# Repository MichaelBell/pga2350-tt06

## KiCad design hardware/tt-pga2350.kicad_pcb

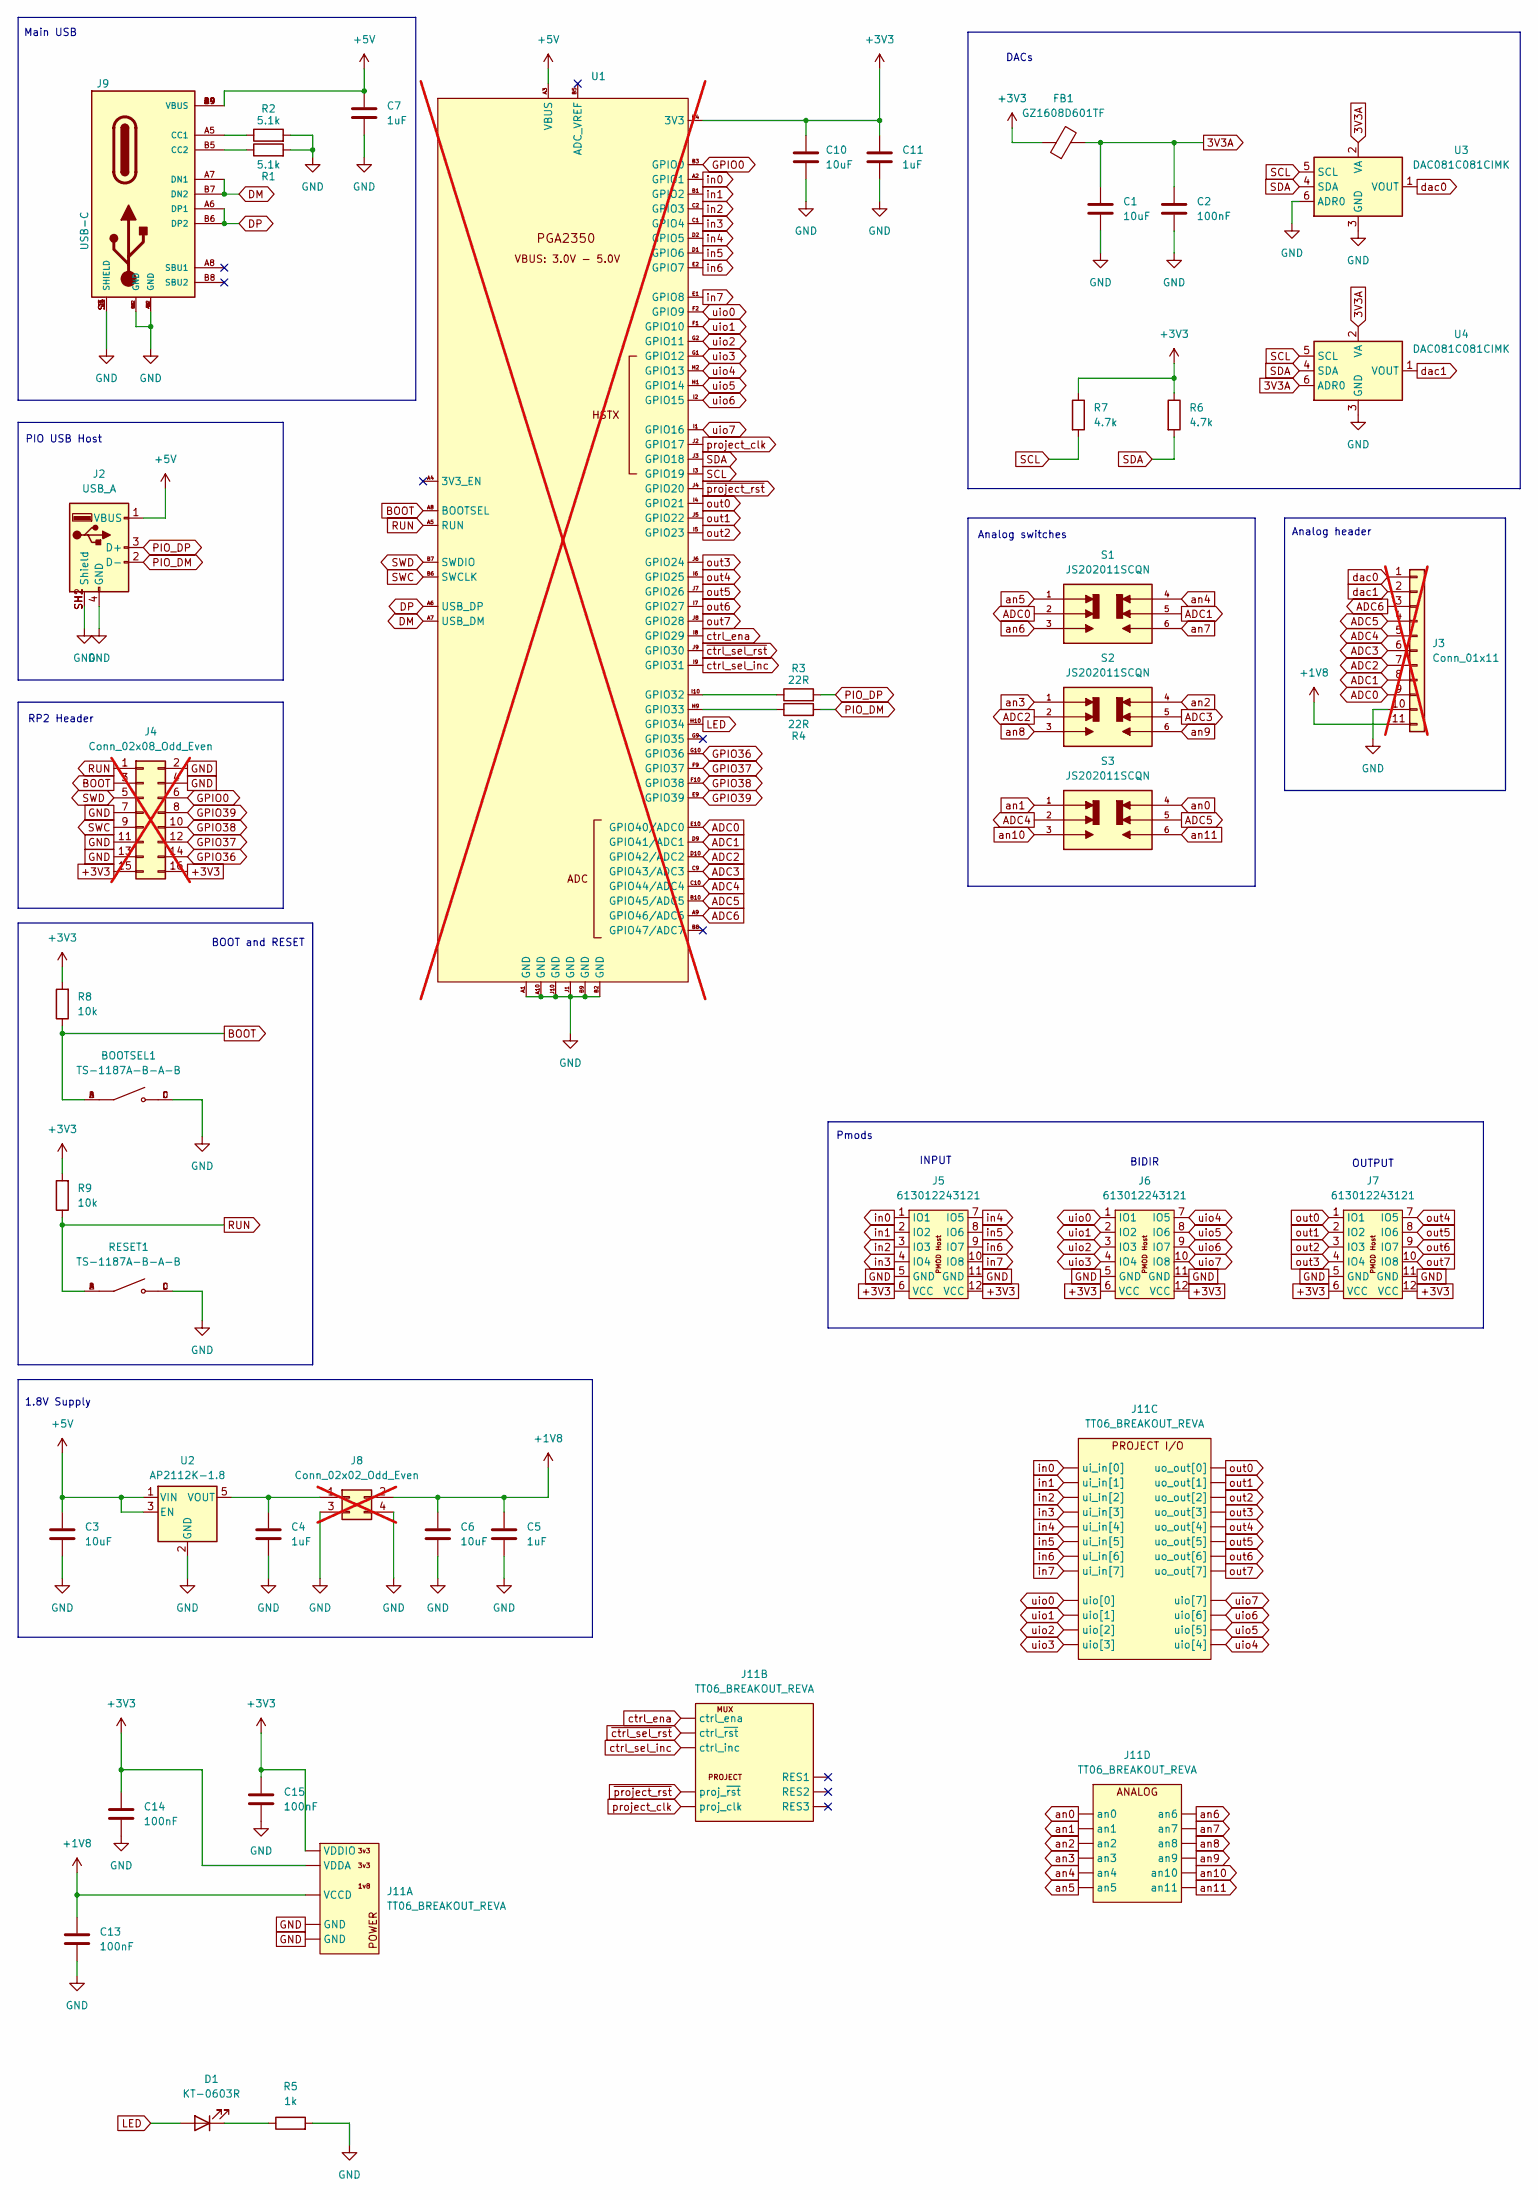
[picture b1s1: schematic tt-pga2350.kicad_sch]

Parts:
BOOTSEL1: TS-1187A-B-A-B; SW_TS-1187A-B-A-B; PARTREV A0
C1, C3, C6, C10: 10uF; C_0603_1608Metric
C2, C13, C14, C15: 100nF; C_0603_1608Metric
C4, C5, C7, C11: 1uF; C_0603_1608Metric
D1: KT-0603R; LED_0603_1608Metric; JLC C2286
FB1: GZ1608D601TF; L_0603_1608Metric
J2: USB_A; TE_292303-1; JLC C86461
J3: Conn_01x11; PinHeader_1x11_P2.54mm_Vertical; not fitted
J4: Conn_02x08_Odd_Even; PinHeader_2x08_P2.54mm_Vertical; not fitted
J5, J6, J7: 613012243121; PinSocket_2x06_P2.54mm_PMODHost1A; LCSC Part # C21262345
J8: Conn_02x02_Odd_Even; PinHeader_2x02_P2.54mm_Vertical; not fitted
J9: USB-C; TYPE-C-SMD_MC-107DJ; MPN USB4500-03-0-A; JLC C3039323
J11: TT06_BREAKOUT_REVA; TT06_CARRIER_ON_DB
R1, R2: 5.1k; R_0603_1608Metric
R3, R4: 22R; R_0603_1608Metric
R5: 1k; R_0603_1608Metric
R6, R7: 4.7k; R_0603_1608Metric
R8, R9: 10k; R_0603_1608Metric
RESET1: TS-1187A-B-A-B; SW_TS-1187A-B-A-B; PARTREV A0
S1, S2, S3: JS202011SCQN; SW_JS202011SCQN; PARTREV 26 May 22
U1: PGA2350; not fitted
U2: AP2112K-1.8; SOT-23-5; JLC C176944
U3, U4: DAC081C081CIMK; SOT-23-6; LCSC Part # C2679618

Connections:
3V3A: C1.1, C2.1, FB1.2, U3.2 (VA), U4.2 (VA), U4.6 (ADR0)
+1V8: C5.1, C6.1, C13.1, J3.11, J8.2, J11.A7 (VCCD)
+3V3: C10.1, C11.1, C14.1, C15.1, FB1.1, J4.15, J4.16, J5.6 (VCC), J5.12 (VCC), J6.6 (VCC), J6.12 (VCC), J7.6 (VCC), J7.12 (VCC), J11.B2 (VDDA), J11.B4 (VDDIO), R6.1, R7.1, R8.2, R9.2, U1.B4 (3V3); also elsewhere on the board
+5V: C3.1, C7.1, J2.1 (VBUS), J9.A4 (VBUS), J9.A9 (VBUS), J9.B4 (VBUS), J9.B9 (VBUS), U1.A3 (VBUS), U2.1 (VIN), U2.3 (EN); also elsewhere on the board
ADC0: J3.9, S1.2, U1.E10 (GPIO40/ADC0); also elsewhere on the board
ADC1: J3.8, S1.5, U1.D9 (GPIO41/ADC1); also elsewhere on the board
ADC2: J3.7, S2.2, U1.D10 (GPIO42/ADC2); also elsewhere on the board
ADC3: J3.6, S2.5, U1.C9 (GPIO43/ADC3); also elsewhere on the board
ADC4: J3.5, S3.2, U1.C10 (GPIO44/ADC4); also elsewhere on the board
ADC5: J3.4, S3.5, U1.B10 (GPIO45/ADC5); also elsewhere on the board
ADC6: J3.3, U1.A9 (GPIO46/ADC6); also elsewhere on the board
BOOT: BOOTSEL1.A, BOOTSEL1.B, J4.3, R8.1, U1.A8 (BOOTSEL); also elsewhere on the board
DM: J9.A7 (DN1), J9.B7 (DN2), U1.A7 (USB_DM); also elsewhere on the board
DP: J9.A6 (DP1), J9.B6 (DP2), U1.A6 (USB_DP); also elsewhere on the board
GND: BOOTSEL1.C, BOOTSEL1.D, C1.2, C2.2, C3.2, C4.2, C5.2, C6.2, C7.2, C10.2, C11.2, C13.2, C14.2, C15.2, J2.4 (GND), J2.SH1 (Shield), J2.SH2 (Shield), J3.10, J4.2, J4.4, J4.7, J4.11, J4.13, J5.5 (GND), J5.11 (GND), J6.5 (GND), J6.11 (GND), J7.5 (GND), J7.11 (GND), J8.3, J8.4, J9.1 (SHIELD), J9.A1 (GND), J9.A12 (GND), J9.B1 (GND), J9.B12 (GND), J9.S1 (SHIELD), J9.S3 (SHIELD), J9.S4 (SHIELD), J11.A1 (GND), J11.A5 (GND), J11.A12 (GND), J11.A15 (GND), J11.A18 (GND), J11.A21 (GND), J11.A23 (GND), J11.A25 (GND), J11.A27 (GND), J11.A29 (GND), J11.A31 (GND), J11.A32 (GND), J11.A33 (GND), J11.A37 (GND), J11.A38 (GND), J11.B1 (GND), J11.B3 (GND), J11.B6 (GND), J11.B8 (GND), J11.B10 (GND), J11.B12 (GND), J11.B14 (GND), J11.B16 (GND), J11.B17 (GND), J11.B18 (GND), J11.B23 (GND), J11.B24 (GND), J11.B29 (GND), J11.B30 (GND), J11.B35 (GND), J11.B36 (GND), J11.B39 (GND), J11.B40 (GND), R1.2, R2.2, R5.2, RESET1.C, RESET1.D, U1.A1 (GND), U1.A10 (GND), U1.B2 (GND), U1.B9 (GND), U1.J1 (GND), U1.J10 (GND), U2.2 (GND), U3.3 (GND), U3.6 (ADR0), U4.3 (GND); also elsewhere on the board
GPIO0: J4.6, U1.B3 (GPIO0); also elsewhere on the board
GPIO36: J4.14, U1.G10 (GPIO36); also elsewhere on the board
GPIO37: J4.12, U1.F9 (GPIO37); also elsewhere on the board
GPIO38: J4.10, U1.F10 (GPIO38); also elsewhere on the board
GPIO39: J4.8, U1.E9 (GPIO39); also elsewhere on the board
LED: D1.2 (A), U1.H10 (GPIO34); also elsewhere on the board
unnamed: D1.1 (K), R5.1
unnamed: C4.1, J8.1, U2.5 (VOUT)
unnamed: J9.A5 (CC1), R2.1
unnamed: J9.B5 (CC2), R1.1
unnamed 25: R3.1, U1.I10 (GPIO32); also elsewhere on the board
unnamed 26: R4.1, U1.H9 (GPIO33); also elsewhere on the board
PIO_DM: J2.2 (D-), R4.2
PIO_DP: J2.3 (D+), R3.2
RUN: J4.1, R9.1, RESET1.A, RESET1.B, U1.A5 (RUN); also elsewhere on the board
SCL: R7.2, U1.I3 (GPIO19), U3.5 (SCL), U4.5 (SCL); also elsewhere on the board
SDA: R6.2, U1.J3 (GPIO18), U3.4 (SDA), U4.4 (SDA); also elsewhere on the board
SWC: J4.9, U1.B6 (SWCLK); also elsewhere on the board
SWD: J4.5, U1.B7 (SWDIO); also elsewhere on the board
an0: J11.A20 (an0), S3.4
an1: J11.A22 (an1), S3.1
an2: J11.A24 (an2), S2.4
an3: J11.A26 (an3), S2.1
an4: J11.A28 (an4), S1.4
an5: J11.A30 (an5), S1.1
an6: J11.B15 (an6), S1.3
an7: J11.B13 (an7), S1.6
an8: J11.B11 (an8), S2.3
an9: J11.B9 (an9), S2.6
an10: J11.B7 (an10), S3.3
an11: J11.B5 (an11), S3.6
ctrl_ena: J11.A2 (ctrl_ena), U1.I8 (GPIO29); also elsewhere on the board
ctrl_sel_inc: J11.A3 (ctrl_inc), U1.I9 (GPIO31); also elsewhere on the board
dac0: J3.1, U3.1 (VOUT)
dac1: J3.2, U4.1 (VOUT)
in0: J5.1 (IO1), J11.A9 (ui_in[0]), U1.A2 (GPIO1); also elsewhere on the board
in1: J5.2 (IO2), J11.A11 (ui_in[1]), U1.B1 (GPIO2); also elsewhere on the board
in2: J5.3 (IO3), J11.A14 (ui_in[2]), U1.C2 (GPIO3); also elsewhere on the board
in3: J5.4 (IO4), J11.A13 (ui_in[3]), U1.C1 (GPIO4); also elsewhere on the board
in4: J5.7 (IO5), J11.A17 (ui_in[4]), U1.D2 (GPIO5); also elsewhere on the board
in5: J5.8 (IO6), J11.A19 (ui_in[5]), U1.D1 (GPIO6); also elsewhere on the board
in6: J5.9 (IO7), J11.A16 (ui_in[6]), U1.E2 (GPIO7); also elsewhere on the board
in7: J5.10 (IO8), J11.A34 (ui_in[7]), U1.E1 (GPIO8); also elsewhere on the board
out0: J7.1 (IO1), J11.B27 (uo_out[0]), U1.I4 (GPIO21); also elsewhere on the board
out1: J7.2 (IO2), J11.B28 (uo_out[1]), U1.J5 (GPIO22); also elsewhere on the board
out2: J7.3 (IO3), J11.B25 (uo_out[2]), U1.I5 (GPIO23); also elsewhere on the board
out3: J7.4 (IO4), J11.B26 (uo_out[3]), U1.J6 (GPIO24); also elsewhere on the board
out4: J7.7 (IO5), J11.B21 (uo_out[4]), U1.I6 (GPIO25); also elsewhere on the board
out5: J7.8 (IO6), J11.B22 (uo_out[5]), U1.J7 (GPIO26); also elsewhere on the board
out6: J7.9 (IO7), J11.B19 (uo_out[6]), U1.I7 (GPIO27); also elsewhere on the board
out7: J7.10 (IO8), J11.B20 (uo_out[7]), U1.J8 (GPIO28); also elsewhere on the board
project_clk: J11.A35 (proj_clk), U1.J2 (GPIO17); also elsewhere on the board
uio0: J6.1 (IO1), J11.A39 (uio[0]), U1.F2 (GPIO9); also elsewhere on the board
uio1: J6.2 (IO2), J11.A40 (uio[1]), U1.F1 (GPIO10); also elsewhere on the board
uio2: J6.3 (IO3), J11.B37 (uio[2]), U1.G2 (GPIO11); also elsewhere on the board
uio3: J6.4 (IO4), J11.B38 (uio[3]), U1.G1 (GPIO12); also elsewhere on the board
uio4: J6.7 (IO5), J11.B33 (uio[4]), U1.H2 (GPIO13); also elsewhere on the board
uio5: J6.8 (IO6), J11.B34 (uio[5]), U1.H1 (GPIO14); also elsewhere on the board
uio6: J6.9 (IO7), J11.B31 (uio[6]), U1.I2 (GPIO15); also elsewhere on the board
uio7: J6.10 (IO8), J11.B32 (uio[7]), U1.I1 (GPIO16); also elsewhere on the board
~ctrl_sel_rst: J11.A4 (ctrl_~rst), U1.J9 (GPIO30); also elsewhere on the board
~project_rst: J11.A36 (proj_~rst), U1.J4 (GPIO20); also elsewhere on the board

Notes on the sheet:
Main USB
BOOT and RESET
1.8V Supply
OUTPUT
Pmods
PIO USB Host
RP2 Header
DACs
Analog switches
BIDIR
Analog header
INPUT

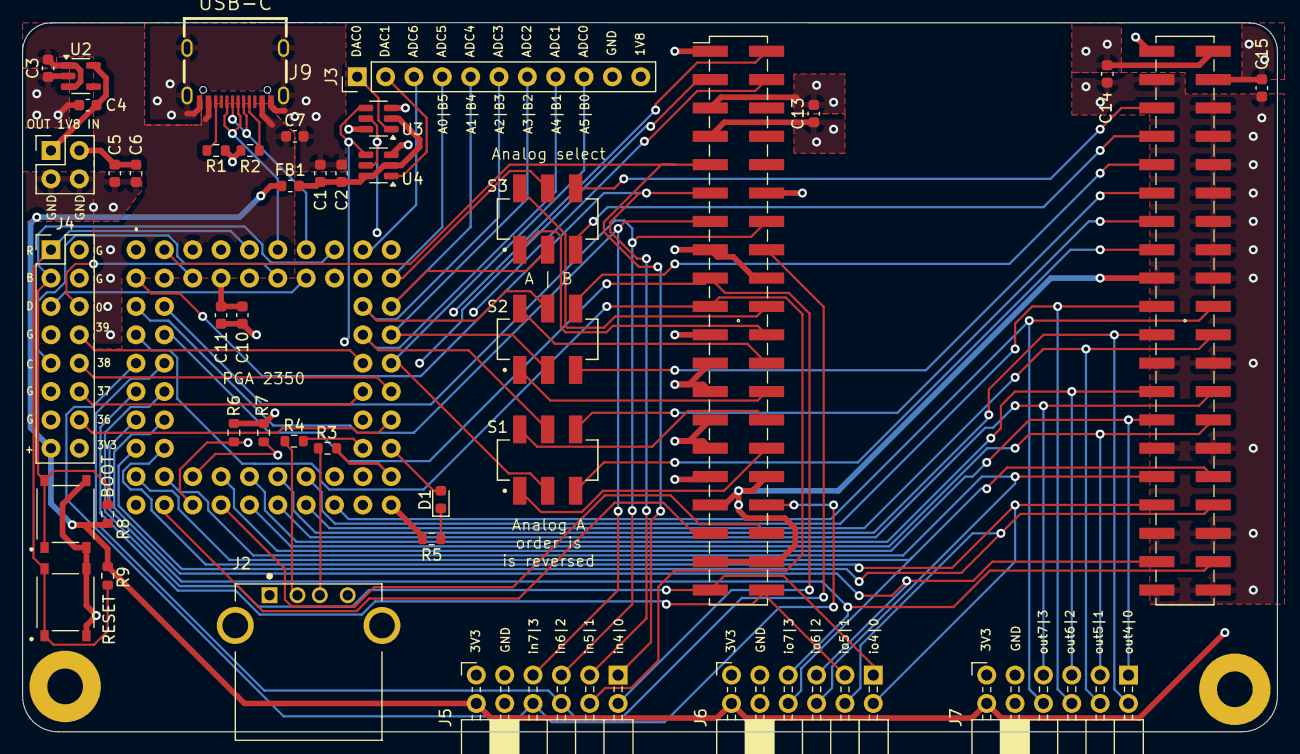
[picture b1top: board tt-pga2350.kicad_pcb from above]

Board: 4 copper layers, 112.4 x 63.5 mm, 41 parts (0 on the bottom side), 77 nets.

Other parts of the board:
BOOT: TS-1187A-B-A-B; SW_TS-1187A-B-A-B
PGA 2350: PGA2350
RESET: TS-1187A-B-A-B; SW_TS-1187A-B-A-B

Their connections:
+3V3: PGA 2350.B4 (3V3); also elsewhere on the board
+5V: PGA 2350.A3 (VBUS); also elsewhere on the board
ADC0: PGA 2350.E10 (GPIO40/ADC0); also elsewhere on the board
ADC1: PGA 2350.D9 (GPIO41/ADC1); also elsewhere on the board
ADC2: PGA 2350.D10 (GPIO42/ADC2); also elsewhere on the board
ADC3: PGA 2350.C9 (GPIO43/ADC3); also elsewhere on the board
ADC4: PGA 2350.C10 (GPIO44/ADC4); also elsewhere on the board
ADC5: PGA 2350.B10 (GPIO45/ADC5); also elsewhere on the board
ADC6: PGA 2350.A9 (GPIO46/ADC6); also elsewhere on the board
BOOT: BOOT.A, BOOT.B, PGA 2350.A8 (BOOTSEL); also elsewhere on the board
DM: PGA 2350.A7 (USB_DM); also elsewhere on the board
DP: PGA 2350.A6 (USB_DP); also elsewhere on the board
GND: BOOT.C, BOOT.D, PGA 2350.A1 (GND), PGA 2350.A10 (GND), PGA 2350.B2 (GND), PGA 2350.B9 (GND), PGA 2350.J1 (GND), PGA 2350.J10 (GND), RESET.C, RESET.D; also elsewhere on the board
GPIO0: PGA 2350.B3 (GPIO0); also elsewhere on the board
GPIO36: PGA 2350.G10 (GPIO36); also elsewhere on the board
GPIO37: PGA 2350.F9 (GPIO37); also elsewhere on the board
GPIO38: PGA 2350.F10 (GPIO38); also elsewhere on the board
GPIO39: PGA 2350.E9 (GPIO39); also elsewhere on the board
LED: PGA 2350.H10 (GPIO34); also elsewhere on the board
unnamed 25: PGA 2350.I10 (GPIO32); also elsewhere on the board
unnamed 26: PGA 2350.H9 (GPIO33); also elsewhere on the board
RUN: PGA 2350.A5 (RUN), RESET.A, RESET.B; also elsewhere on the board
SCL: PGA 2350.I3 (GPIO19); also elsewhere on the board
SDA: PGA 2350.J3 (GPIO18); also elsewhere on the board
SWC: PGA 2350.B6 (SWCLK); also elsewhere on the board
SWD: PGA 2350.B7 (SWDIO); also elsewhere on the board
ctrl_ena: PGA 2350.I8 (GPIO29); also elsewhere on the board
ctrl_sel_inc: PGA 2350.I9 (GPIO31); also elsewhere on the board
in0: PGA 2350.A2 (GPIO1); also elsewhere on the board
in1: PGA 2350.B1 (GPIO2); also elsewhere on the board
in2: PGA 2350.C2 (GPIO3); also elsewhere on the board
in3: PGA 2350.C1 (GPIO4); also elsewhere on the board
in4: PGA 2350.D2 (GPIO5); also elsewhere on the board
in5: PGA 2350.D1 (GPIO6); also elsewhere on the board
in6: PGA 2350.E2 (GPIO7); also elsewhere on the board
in7: PGA 2350.E1 (GPIO8); also elsewhere on the board
out0: PGA 2350.I4 (GPIO21); also elsewhere on the board
out1: PGA 2350.J5 (GPIO22); also elsewhere on the board
out2: PGA 2350.I5 (GPIO23); also elsewhere on the board
out3: PGA 2350.J6 (GPIO24); also elsewhere on the board
out4: PGA 2350.I6 (GPIO25); also elsewhere on the board
out5: PGA 2350.J7 (GPIO26); also elsewhere on the board
out6: PGA 2350.I7 (GPIO27); also elsewhere on the board
out7: PGA 2350.J8 (GPIO28); also elsewhere on the board
project_clk: PGA 2350.J2 (GPIO17); also elsewhere on the board
uio0: PGA 2350.F2 (GPIO9); also elsewhere on the board
uio1: PGA 2350.F1 (GPIO10); also elsewhere on the board
uio2: PGA 2350.G2 (GPIO11); also elsewhere on the board
uio3: PGA 2350.G1 (GPIO12); also elsewhere on the board
uio4: PGA 2350.H2 (GPIO13); also elsewhere on the board
uio5: PGA 2350.H1 (GPIO14); also elsewhere on the board
uio6: PGA 2350.I2 (GPIO15); also elsewhere on the board
uio7: PGA 2350.I1 (GPIO16); also elsewhere on the board
~ctrl_sel_rst: PGA 2350.J9 (GPIO30); also elsewhere on the board
~project_rst: PGA 2350.J4 (GPIO20); also elsewhere on the board

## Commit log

2024-10-17 Initial testing
2024-10-18 Add board design files
2024-10-18 HSTX testing
2024-10-18 Move ttcontrol and dac modules to default filesystem
